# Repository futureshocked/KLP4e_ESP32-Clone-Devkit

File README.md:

# KLP4e_ESP32-Clone-Devkit

This is the repository for the "ESP32 devikit clone" project.

This is one of the projects from the course [KiCad Like a Pro, 4th edition](https://techexplorations.com/so/kicad-like-a-pro-4th-edition).

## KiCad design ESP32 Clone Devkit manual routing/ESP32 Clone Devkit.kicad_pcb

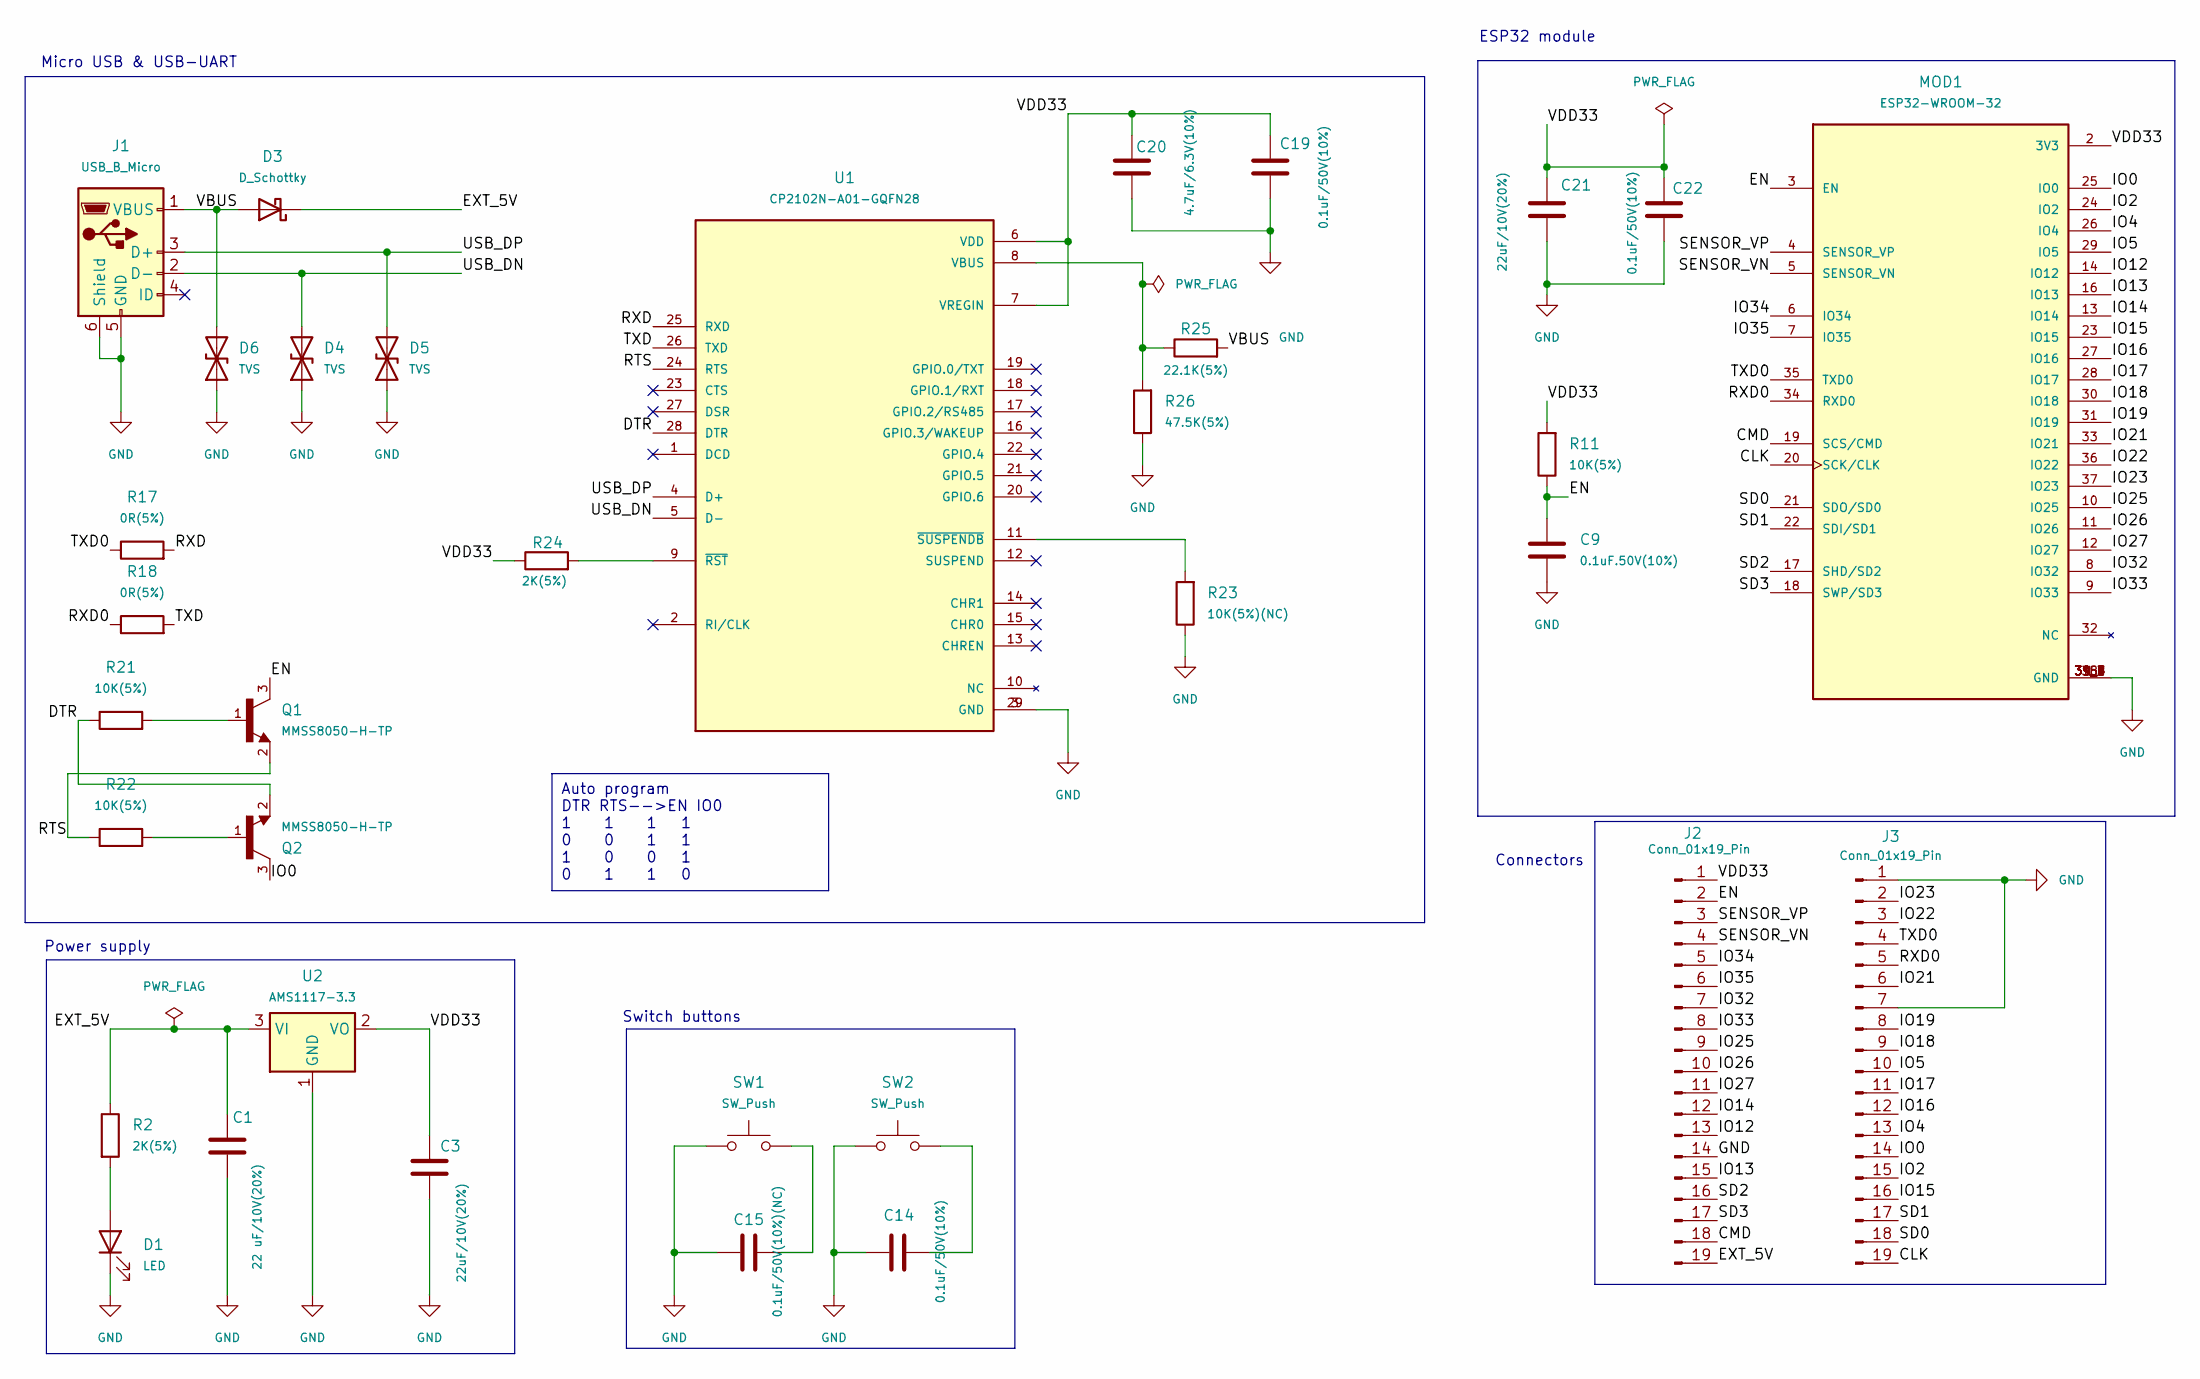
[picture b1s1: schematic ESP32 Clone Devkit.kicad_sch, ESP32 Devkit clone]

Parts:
C1: 22 uF/10V(20%); C_0603_1608Metric
C3, C21: 22uF/10V(20%); C_0603_1608Metric
C9: 0.1uF.50V(10%); C_0402_1005Metric
C14, C19, C22: 0.1uF/50V(10%); C_0402_1005Metric
C15: 0.1uF/50V(10%)(NC); C_0402_1005Metric
C20: 4.7uF/6.3V(10%); C_0402_1005Metric
D1: LED; LED_0603_1608Metric
D3: D_Schottky; D_SOD-323
D4, D5, D6: TVS; D_SOD-323
J1: USB_B_Micro; USB_Micro-AB_Molex_47590-0001
J2, J3: Conn_01x19_Pin; PinHeader_1x19_P2.54mm_Vertical
MOD1: ESP32-WROOM-32; MODULE_ESP32-WROOM-32; PARTREV 2.9
Q1, Q2: MMSS8050-H-TP; TRANS_MMSS8050-H-TP; PARTREV D
R2, R24: 2K(5%); R_0402_1005Metric
R11, R21, R22: 10K(5%); R_0402_1005Metric
R17, R18: 0R(5%); R_0402_1005Metric
R23: 10K(5%)(NC); R_0402_1005Metric
R25: 22.1K(5%); R_0402_1005Metric
R26: 47.5K(5%); R_0402_1005Metric
SW1, SW2: SW_Push; SW_SPST_B3S-1000
U1: CP2102N-A01-GQFN28; QFN50P500X500X80-29N; PARTREV 1.0
U2: AMS1117-3.3; SOT-223-3_TabPin2

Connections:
/CLK: J3.19, MOD1.20 (SCK/CLK)
/CMD: J2.18, MOD1.19 (SCS/CMD)
/DTR: Q2.2, R21.1, U1.28 (DTR)
/EN: C9.1, J2.2, MOD1.3 (EN), Q1.3, R11.1
/EXT_5V: C1.1, D3.1 (K), J2.19, R2.1, U2.3 (VI)
/IO0: J3.14, MOD1.25 (IO0), Q2.3
/IO2: J3.15, MOD1.24 (IO2)
/IO4: J3.13, MOD1.26 (IO4)
/IO5: J3.10, MOD1.29 (IO5)
/IO12: J2.13, MOD1.14 (IO12)
/IO13: J2.15, MOD1.16 (IO13)
/IO14: J2.12, MOD1.13 (IO14)
/IO15: J3.16, MOD1.23 (IO15)
/IO16: J3.12, MOD1.27 (IO16)
/IO17: J3.11, MOD1.28 (IO17)
/IO18: J3.9, MOD1.30 (IO18)
/IO19: J3.8, MOD1.31 (IO19)
/IO21: J3.6, MOD1.33 (IO21)
/IO22: J3.3, MOD1.36 (IO22)
/IO23: J3.2, MOD1.37 (IO23)
/IO25: J2.9, MOD1.10 (IO25)
/IO26: J2.10, MOD1.11 (IO26)
/IO27: J2.11, MOD1.12 (IO27)
/IO32: J2.7, MOD1.8 (IO32)
/IO33: J2.8, MOD1.9 (IO33)
/IO34: J2.5, MOD1.6 (IO34)
/IO35: J2.6, MOD1.7 (IO35)
/RTS: Q1.2, R22.1, U1.24 (RTS)
/RXD: R17.2, U1.25 (RXD)
/RXD0: J3.5, MOD1.34 (RXD0), R18.1
/SD0: J3.18, MOD1.21 (SDO/SD0)
/SD1: J3.17, MOD1.22 (SDI/SD1)
/SD2: J2.16, MOD1.17 (SHD/SD2)
/SD3: J2.17, MOD1.18 (SWP/SD3)
/SENSOR_VN: J2.4, MOD1.5 (SENSOR_VN)
/SENSOR_VP: J2.3, MOD1.4 (SENSOR_VP)
/TXD: R18.2, U1.26 (TXD)
/TXD0: J3.4, MOD1.35 (TXD0), R17.1
/USB_DN: D4.2 (A2), J1.2 (D-), U1.5 (D-)
/USB_DP: D5.2 (A2), J1.3 (D+), U1.4 (D+)
/VBUS: D3.2 (A), D6.2 (A2), J1.1 (VBUS), R25.2
/VDD33: C3.1, C19.1, C20.1, C21.1, C22.1, J2.1, MOD1.2 (3V3), R11.2, R24.1, U1.6 (VDD), U1.7 (VREGIN), U2.2 (VO)
GND: C1.2, C3.2, C9.2, C14.1, C15.1, C19.2, C20.2, C21.2, C22.2, D1.1 (K), D4.1 (A1), D5.1 (A1), D6.1 (A1), J1.5 (GND), J1.6 (Shield), J2.14, J3.1, J3.7, MOD1.1 (GND), MOD1.15 (GND), MOD1.38 (GND), MOD1.39_1 (GND), MOD1.39_2 (GND), MOD1.39_3 (GND), MOD1.39_4 (GND), MOD1.39_5 (GND), MOD1.39_6 (GND), MOD1.39_7 (GND), MOD1.39_8 (GND), MOD1.39_9 (GND), R23.1, R26.1, SW1.1, SW2.1, U1.3 (GND), U1.29 (GND), U2.1 (GND)
unnamed: C14.2, SW2.2
unnamed: C15.2, SW1.2
unnamed: D1.2 (A), R2.2
unnamed: Q1.1, R21.2
unnamed: Q2.1, R22.2
unnamed: R25.1, R26.2, U1.8 (VBUS)
unnamed: R24.2, U1.9 (~RST)
unnamed: R23.2, U1.11 (~SUSPENDB)

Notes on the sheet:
Auto program DTR RTS-->EN IO0 1 1 1 1 0 0 1 1 1 0 0 1 0 1 1 0
Switch buttons
Connectors
ESP32 module
Power supply
Micro USB & USB-UART

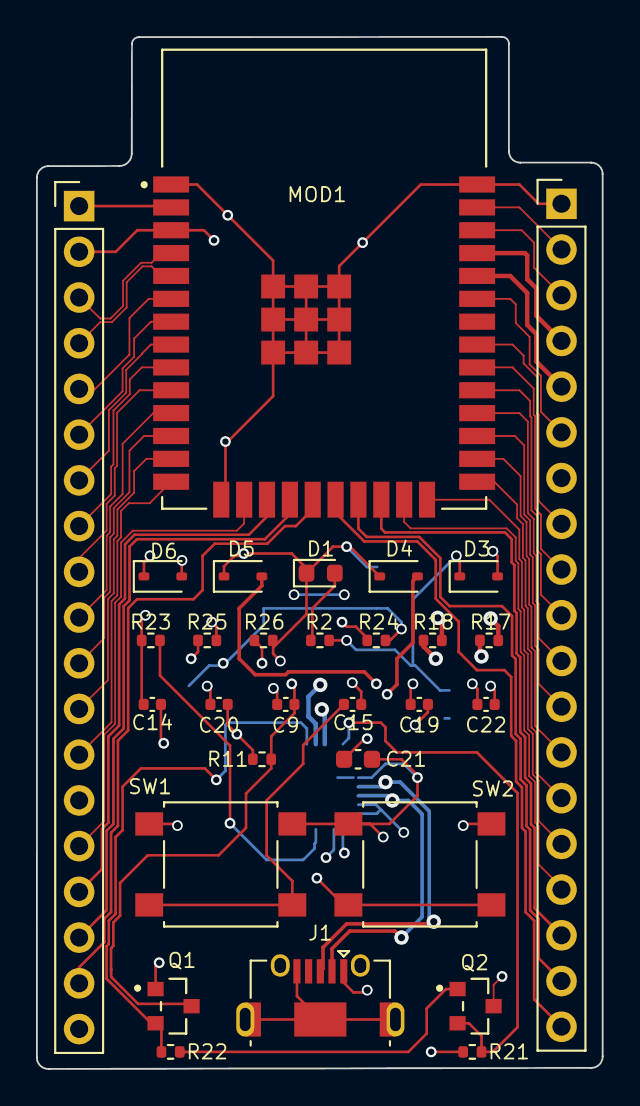
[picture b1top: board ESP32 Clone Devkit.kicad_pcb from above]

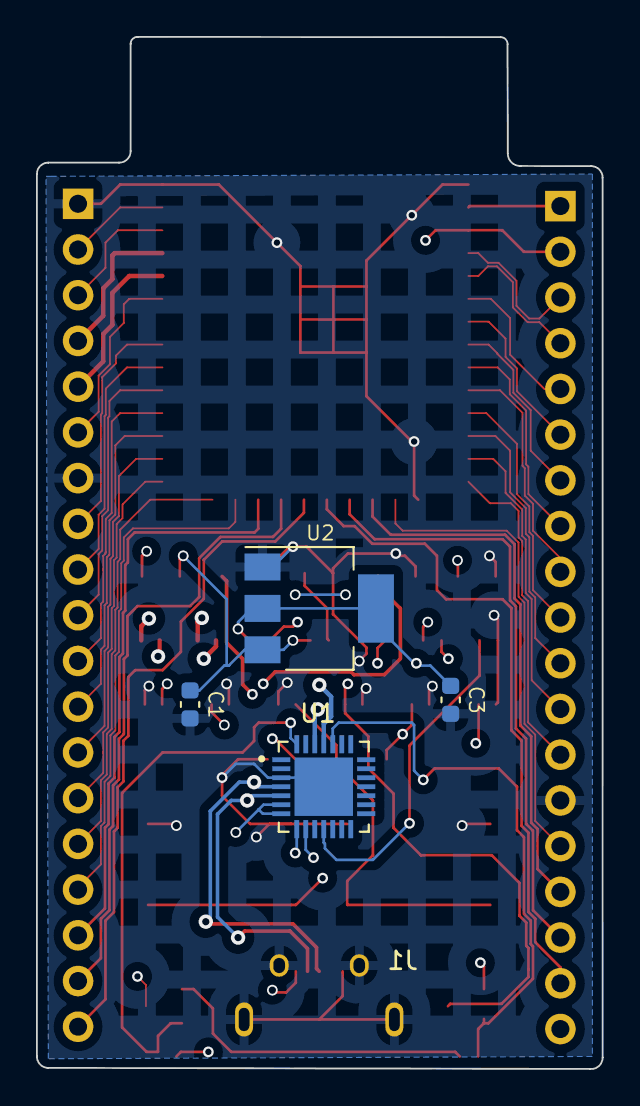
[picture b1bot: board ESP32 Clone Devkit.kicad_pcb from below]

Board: 4 copper layers, 31.4 x 57.3 mm, 34 parts (4 on the bottom side), 51 nets.
